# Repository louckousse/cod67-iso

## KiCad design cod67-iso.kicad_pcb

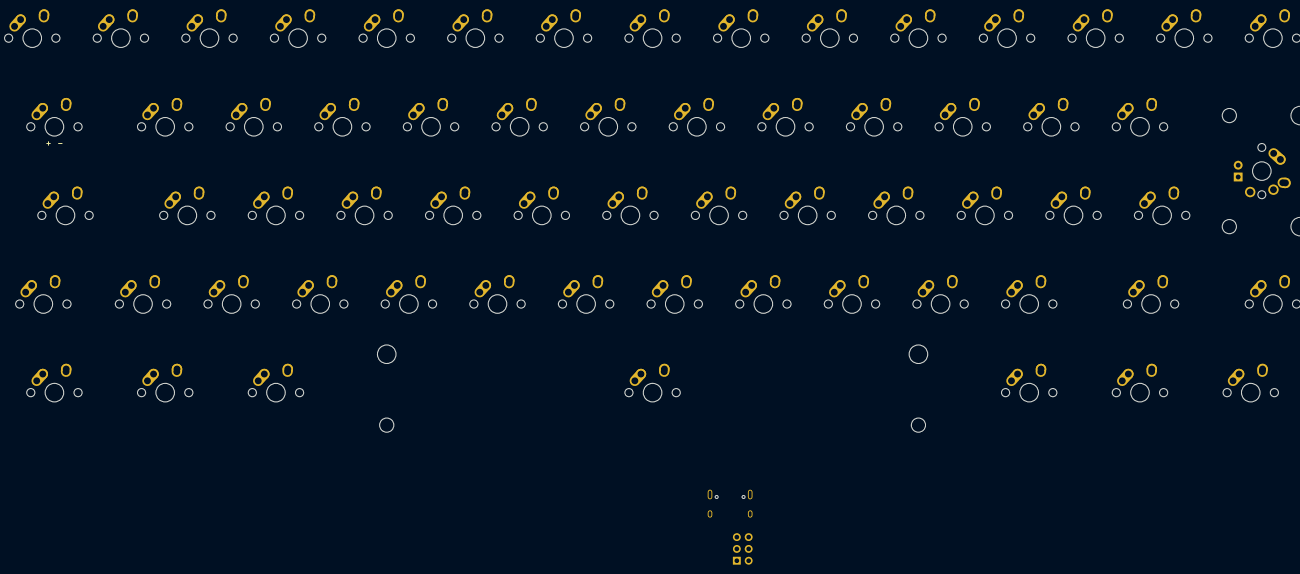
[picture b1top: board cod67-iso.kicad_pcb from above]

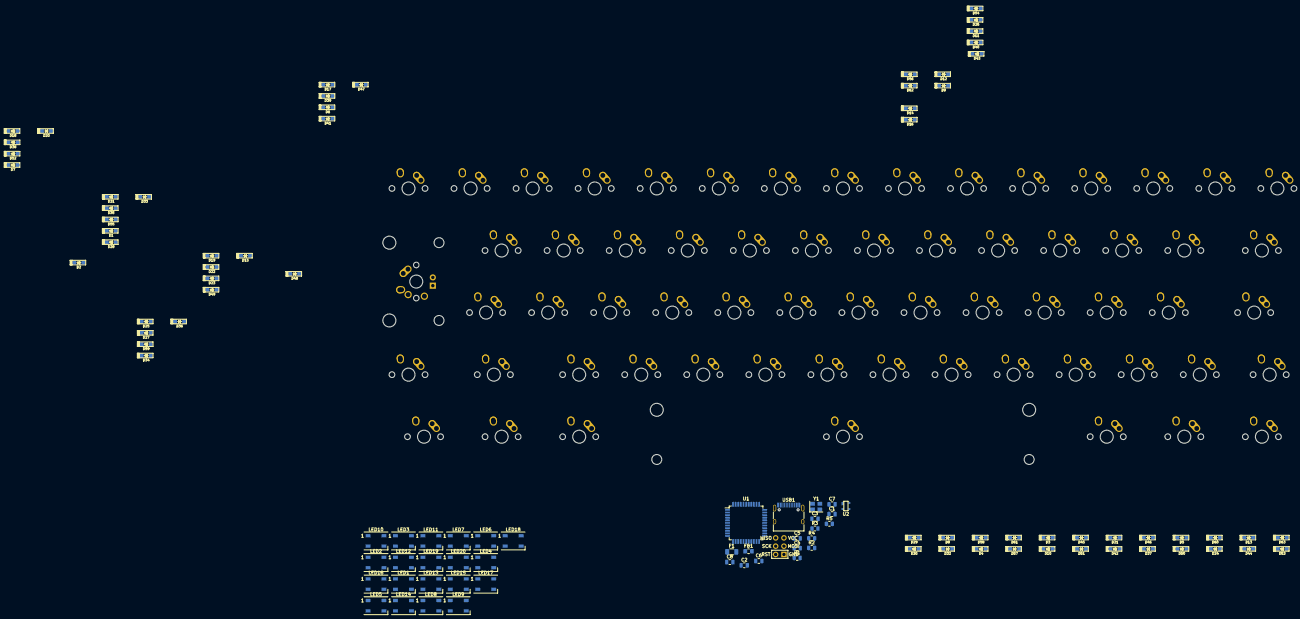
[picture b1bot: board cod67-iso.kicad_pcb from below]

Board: 2 copper layers, 166 parts (103 on the bottom side), 89 nets, no tracks yet.

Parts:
C1: 1uF; C_0805_2012Metric
C2, C3: 22pF; C_0805_2012Metric
C4, C5, C6, C7: 0.1uF; C_0805_2012Metric
C8: 10uF; C_0805_2012Metric
D1: D_Small; D_SOD123F
D2, D3, D4, D5, D6, D7, D8, D9, D10, D11, D12, D13, D14, D15, D16, D17, D18, D19, D20, D21, D22, D23, D24, D25, D26, D27, D28, D29, D30, D31, D32, D33, D34, D35, D36, D37, D38, D39, D40, D41, D42, D43, D44, D45, D46, D47, D48, D49, D50, D51, D52, D53, D54, D55, D56, D57, D58, D59, D60, D61, D62, D63: D_SOD123F
F1: 500mA; Fuse_1206_3216Metric
FB1: Ferrite_Bead_Small; L_0805_2012Metric_Pad1.15x1.40mm_HandSolder
J1: AVR-ISP-6; Reset_Pretty-Mask
LED1, LED2, LED3, LED4, LED5, LED6, LED7, LED8, LED9, LED10, LED11, LED12, LED13, LED14, LED15, LED16, LED17, LED18, LED19, LED20: LED_WS2812B_PLCC4_5.0x5.0mm_P3.2mm
MX1: MX-NoLED; MX-1U-NoLED
MX2, MX3, MX4, MX5, MX6, MX7, MX8, MX9, MX10, MX11, MX12, MX13, MX14, MX15, MX17, MX18, MX19, MX20, MX21, MX22, MX23, MX24, MX25, MX26, MX27, MX28, MX31, MX32, MX33, MX34, MX35, MX36, MX37, MX38, MX39, MX40, MX41, MX42, MX44, MX45, MX46, MX47, MX48, MX49, MX50, MX51, MX52, MX53, MX54, MX56, MX58, MX62: MX-1U-NoLED
MX16, MX57, MX59, MX61, MX63: MX-1.5U-NoLED
MX29: MX-ISO
MX30, MX55: MX-1.75U-NoLED
MX43: MX-1.25U-NoLED
MX60: MX-7U-ReversedStabilizers-NoLED
R1: 10k; R_0805_2012Metric
R2, R3: 5.1k; R_0805_2012Metric
R4, R5: 22; R_0805_2012Metric
U1: ATmega32U4-AU; TQFP-44_10x10mm_P0.8mm
U2: PRTR5V0U2X; SOT143B
USB1: USB_C_Receptacle_USB2.0; USB_C_Receptacle_HRO_TYPE-C-31-M-12
Y1: 16MHz; Crystal_SMD_3225-4Pin_3.2x2.5mm

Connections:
COL1: MX1.1 (COL), MX16.1 (COL), MX30.1 (COL), MX43.1 (COL), MX57.1 (COL)
COL2: MX2.1 (COL), MX17.1 (COL), MX31.1 (COL), MX44.1 (COL), MX58.1 (COL)
COL3: MX3.1 (COL), MX18.1 (COL), MX32.1 (COL), MX45.1 (COL), MX59.1 (COL)
COL4: MX4.1 (COL), MX19.1 (COL), MX33.1 (COL), MX46.1 (COL)
COL5: MX5.1 (COL), MX20.1 (COL), MX34.1 (COL), MX47.1 (COL)
COL6: MX6.1 (COL), MX21.1 (COL), MX35.1 (COL), MX48.1 (COL), MX60.1 (COL)
COL7: MX7.1 (COL), MX22.1 (COL), MX36.1 (COL), MX49.1 (COL)
COL8: MX8.1 (COL), MX23.1 (COL), MX37.1 (COL), MX50.1 (COL)
COL9: MX9.1 (COL), MX24.1 (COL), MX38.1 (COL), MX51.1 (COL)
COL10: MX10.1 (COL), MX25.1 (COL), MX39.1 (COL), MX52.1 (COL)
COL11: MX11.1 (COL), MX26.1 (COL), MX40.1 (COL), MX53.1 (COL)
COL12: MX12.1 (COL), MX27.1 (COL), MX41.1 (COL), MX54.1 (COL)
COL13: MX13.1 (COL), MX28.1 (COL), MX42.1 (COL), MX55.1 (COL), MX61.1 (COL)
COL14: MX14.1 (COL), MX29.1 (COL), MX56.1 (COL), MX62.1 (COL)
COL15: MX15.1 (COL), MX63.1 (COL)
unnamed: C7.2, C8.2
unnamed: D1.2 (A), MX1.2 (ROW)
unnamed: D2.2 (A), MX2.2 (ROW)
unnamed: D3.2 (A), MX3.2 (ROW)
unnamed: D4.2 (A), MX4.2 (ROW)
unnamed: D5.2 (A), MX5.2 (ROW)
unnamed: D6.2 (A), MX6.2 (ROW)
unnamed: D7.2 (A), MX7.2 (ROW)
unnamed: D8.2 (A), MX8.2 (ROW)
unnamed: D9.2 (A), MX9.2 (ROW)
unnamed: D10.2 (A), MX10.2 (ROW)
unnamed: D11.2 (A), MX11.2 (ROW)
unnamed: D12.2 (A), MX12.2 (ROW)
unnamed: D13.2 (A), MX13.2 (ROW)
unnamed: D14.2 (A), MX14.2 (ROW)
unnamed: D15.2 (A), MX15.2 (ROW)
unnamed: D16.2 (A), MX16.2 (ROW)
unnamed: D17.2 (A), MX17.2 (ROW)
unnamed: D18.2 (A), MX18.2 (ROW)
unnamed: D19.2 (A), MX19.2 (ROW)
unnamed: D20.2 (A), MX20.2 (ROW)
unnamed: D21.2 (A), MX21.2 (ROW)
unnamed: D22.2 (A), MX22.2 (ROW)
unnamed: D23.2 (A), MX23.2 (ROW)
unnamed: D24.2 (A), MX24.2 (ROW)
unnamed: D25.2 (A), MX25.2 (ROW)
unnamed: D26.2 (A), MX26.2 (ROW)
unnamed: D27.2 (A), MX27.2 (ROW)
unnamed: D28.2 (A), MX28.2 (ROW)
unnamed: D29.2 (A), MX29.2 (ROW)
unnamed: D30.2 (A), MX30.2 (ROW)
unnamed: D31.2 (A), MX31.2 (ROW)
unnamed: D32.2 (A), MX32.2 (ROW)
unnamed: D33.2 (A), MX33.2 (ROW)
unnamed: D34.2 (A), MX34.2 (ROW)
unnamed: D35.2 (A), MX35.2 (ROW)
unnamed: D36.2 (A), MX36.2 (ROW)
unnamed: D37.2 (A), MX37.2 (ROW)
unnamed: D38.2 (A), MX38.2 (ROW)
unnamed: D39.2 (A), MX39.2 (ROW)
unnamed: D40.2 (A), MX40.2 (ROW)
unnamed: D41.2 (A), MX41.2 (ROW)
unnamed: D42.2 (A), MX42.2 (ROW)
unnamed: D43.2 (A), MX43.2 (ROW)
unnamed: D44.2 (A), MX44.2 (ROW)
unnamed: D45.2 (A), MX45.2 (ROW)
unnamed: D46.2 (A), MX46.2 (ROW)
unnamed: D47.2 (A), MX47.2 (ROW)
unnamed: D48.2 (A), MX48.2 (ROW)
unnamed: D49.2 (A), MX49.2 (ROW)
unnamed: D50.2 (A), MX50.2 (ROW)
unnamed: D51.2 (A), MX51.2 (ROW)
unnamed: D52.2 (A), MX52.2 (ROW)
unnamed: D53.2 (A), MX53.2 (ROW)
unnamed: D54.2 (A), MX54.2 (ROW)
unnamed: D55.2 (A), MX55.2 (ROW)
unnamed: D56.2 (A), MX56.2 (ROW)
unnamed: D57.2 (A), MX57.2 (ROW)
unnamed: D58.2 (A), MX58.2 (ROW)
unnamed: D59.2 (A), MX59.2 (ROW)
unnamed: D60.2 (A), MX60.2 (ROW)
unnamed: D61.2 (A), MX61.2 (ROW)
unnamed: D62.2 (A), MX62.2 (ROW)
unnamed: D63.2 (A), MX63.2 (ROW)
unnamed: LED9.4 (DIN), LED10.2 (DOUT)
unnamed: LED6.2 (DOUT), LED11.4 (DIN)
unnamed: LED12.2 (DOUT), LED13.4 (DIN)
unnamed: LED17.4 (DIN), LED18.2 (DOUT)
unnamed: R1.2, U1.33 (~HWB/PE2)
ROW1: D1.1 (K), D2.1 (K), D3.1 (K), D4.1 (K), D5.1 (K), D6.1 (K), D7.1 (K), D8.1 (K), D9.1 (K), D10.1 (K), D11.1 (K), D12.1 (K), D13.1 (K), D14.1 (K), D15.1 (K)
ROW2: D16.1 (K), D17.1 (K), D18.1 (K), D19.1 (K), D20.1 (K), D21.1 (K), D22.1 (K), D23.1 (K), D24.1 (K), D25.1 (K), D26.1 (K), D27.1 (K), D28.1 (K), D29.1 (K)
ROW3: D30.1 (K), D31.1 (K), D32.1 (K), D33.1 (K), D34.1 (K), D35.1 (K), D36.1 (K), D37.1 (K), D38.1 (K), D39.1 (K), D40.1 (K), D41.1 (K), D42.1 (K)
ROW4: D43.1 (K), D44.1 (K), D45.1 (K), D46.1 (K), D47.1 (K), D48.1 (K), D49.1 (K), D50.1 (K), D51.1 (K), D52.1 (K), D53.1 (K), D54.1 (K), D55.1 (K), D56.1 (K)
ROW5: D57.1 (K), D58.1 (K), D59.1 (K), D60.1 (K), D61.1 (K), D62.1 (K), D63.1 (K)

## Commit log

2022-03-30 create schema and places switches
    TODO:
    - add compat
    - change mcu
    - place other comp
2022-04-12 no commit in between is bad
2022-04-15 review from plutonium
2022-04-16 review from plutonium, routing leds
2022-04-19 change 0402 footprint to 0805 ones
2023-06-26 final
